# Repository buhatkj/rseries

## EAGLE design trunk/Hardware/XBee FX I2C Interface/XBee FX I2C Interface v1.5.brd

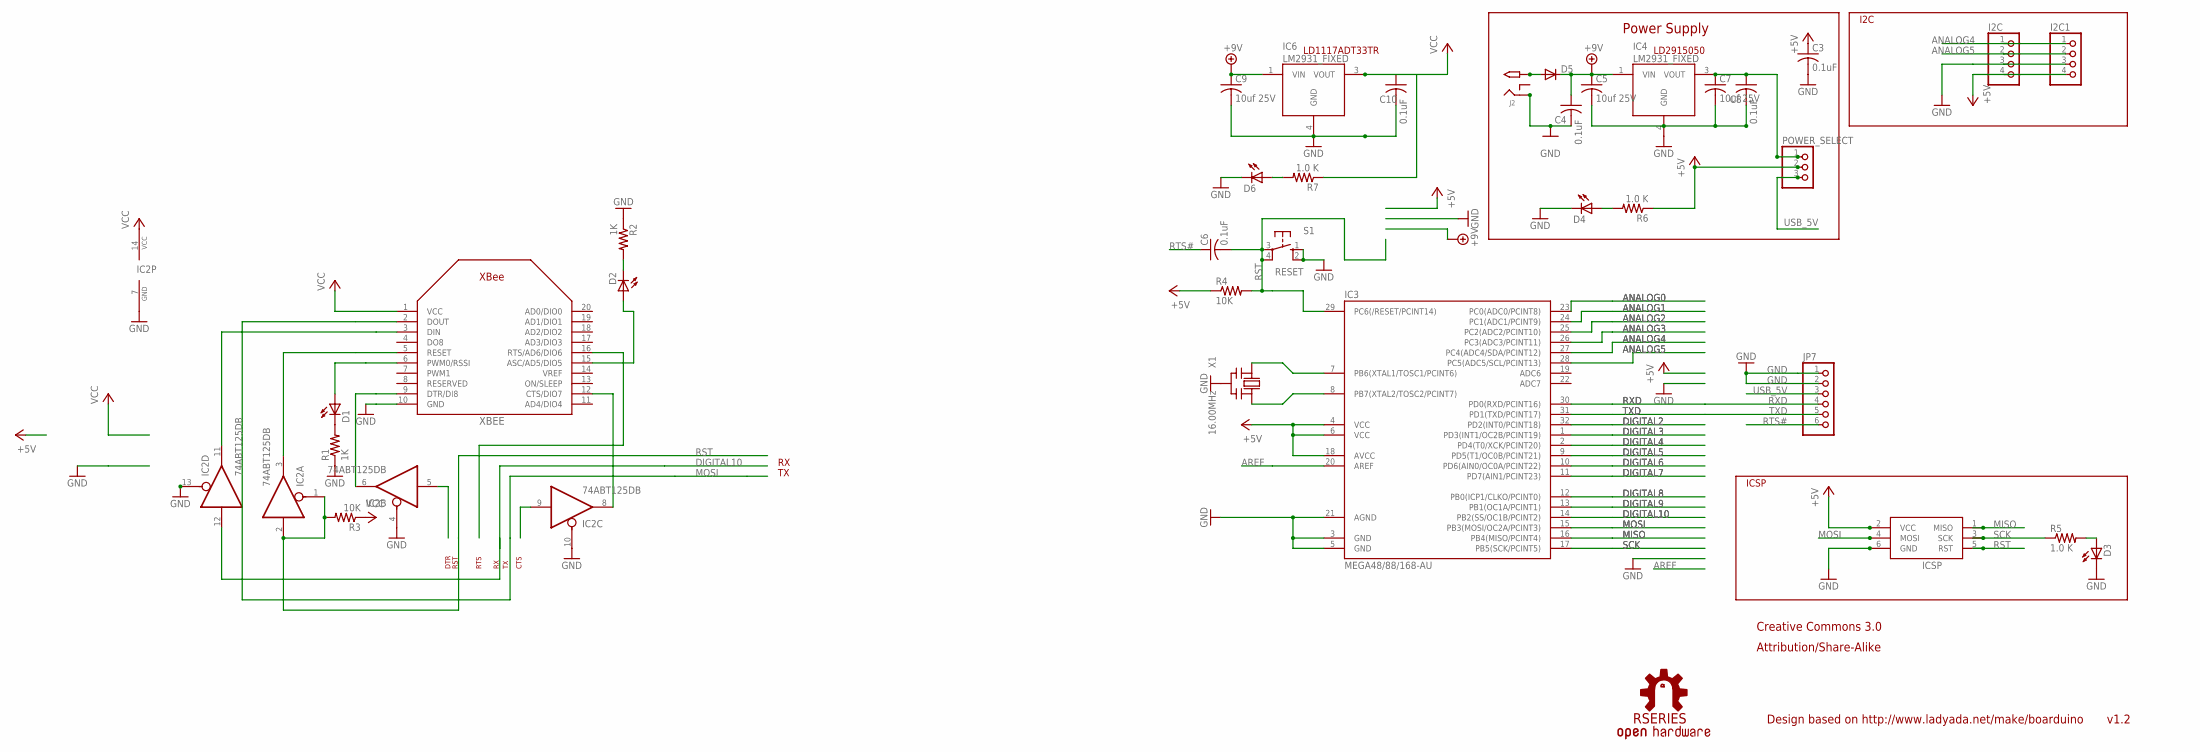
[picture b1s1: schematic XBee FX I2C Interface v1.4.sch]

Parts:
C3, C4, C6, C8, C10: 0.1uF; C1206K
C5, C7, C9: 10uf 25V; C1206K
D1, D2, D4, D6: LEDCHIPLED_1206; CHIPLED_1206
D3: RED; CHIPLED_1206
D5: DIODE-SMB; SMB
I2C, I2C1: PINHD-1X4CB; 1X04-CB
IC2: 74ABT125DB; SSOP14
IC3: MEGA48/88/168-AU; TQFP32-08
IC4, IC6: LM2931_FIXED; DPAK
ICSP: AVRISP-6; AVRISP
J2: 2.1MMJACK; PJ-102A
JP7: PINHD-1X6CLEAN; 1X06-CLEAN
POWER_SELECT: PINHD-1X3; 1X03
R1, R2: 1K; R1206
R3, R4: 10K; R1206
R5, R6, R7: 1.0 K; M1206
S1: RESET; B3F-10XX
U$6: RSERIES-OSHW-LOGOMEDIUM; RSERIES-OSHW-LOGO-MEDIUM
X1: 16.00MHz; CERM_OSC
XBEE: XBEE

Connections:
+3V3: C10.1, IC2.14 (VCC), IC6.3 (VOUT), R3.1, R7.1, XBEE.1 (VCC)
ANALOG0: IC3.23 (PC0(ADC0/PCINT8))
ANALOG1: IC3.24 (PC1(ADC1/PCINT9))
ANALOG2: IC3.25 (PC2(ADC2/PCINT10))
ANALOG3: IC3.26 (PC3(ADC3/PCINT11))
ANALOG4: I2C.1, I2C1.1, IC3.27 (PC4(ADC4/SDA/PCINT12))
ANALOG5: I2C.2, I2C1.2, IC3.28 (PC5(ADC5/SCL/PCINT13))
AREF: IC3.20 (AREF)
DIGITAL2: IC3.32 (PD2(INT0/PCINT18))
DIGITAL3: IC3.1 (PD3(INT1/OC2B/PCINT19))
DIGITAL4: IC3.2 (PD4(T0/XCK/PCINT20))
DIGITAL5: IC3.9 (PD5(T1/OC0B/PCINT21))
DIGITAL6: IC3.10 (PD6(AIN0/OC0A/PCINT22))
DIGITAL7: IC3.11 (PD7(AIN1/PCINT23))
DIGITAL8: IC3.12 (PB0(ICP1/CLKO/PCINT0))
DIGITAL9: IC3.13 (PB1(OC1A/PCINT1))
DIGITAL10: IC2.12 (I), IC3.14 (PB2(SS/OC1B/PCINT2))
GND: C3.2, C4.2, C9.2, C10.2, D3.C, D4.C, D6.C, I2C.3, I2C1.3, IC2.4 (OE), IC2.7 (GND), IC2.10 (OE), IC2.13 (OE), IC3.3 (GND), IC3.5 (GND), IC3.21 (AGND), IC4.4 (GND), IC6.4 (GND), ICSP.6 (GND), J2.RING, JP7.1, JP7.2, R1.1, R2.1, S1.1 (S), S1.2 (S1), X1.P$2 (GND), XBEE.10 (GND)
MISO: IC3.16 (PB4(MISO/PCINT4)), ICSP.1 (MISO)
MOSI: IC3.15 (PB3(MOSI/OC2A/PCINT3)), ICSP.4 (MOSI), XBEE.2 (DOUT)
unnamed: IC2.11 (O), XBEE.3 (DIN)
unnamed: D2.C, R2.2
unnamed: D6.A, R7.2
unnamed: D1.A, XBEE.6 (PWM0/RSSI)
unnamed: D1.C, R1.2
unnamed: IC2.6 (O), XBEE.9 (DTR/DI8)
unnamed: IC2.3 (O), XBEE.5 (RESET)
unnamed: IC2.8 (O), XBEE.12 (CTS/DIO7)
unnamed: D2.A, XBEE.15 (ASC/AD5/DIO5)
unnamed: IC3.7 (PB6(XTAL1/TOSC1/PCINT6)), X1.P$1 (IN)
unnamed: IC3.8 (PB7(XTAL2/TOSC2/PCINT7)), X1.P$3 (OUT)
unnamed: D3.A, R5.2
unnamed: D4.A, R6.2
unnamed: D5.A, J2.TIP
unnamed: C5.2, C7.2, C8.2
unnamed 40: C7.1, C8.1, IC4.3 (VOUT), POWER_SELECT.1; also elsewhere on the board
RST: C6.2, IC2.1 (OE), IC2.2 (I), IC3.29 (PC6(/RESET/PCINT14)), ICSP.5 (RST), R3.2, R4.2, S1.3, S1.4 (P1); also elsewhere on the board
RTS: XBEE.16 (RTS/AD6/DIO6)
RTS#: C6.1, JP7.6
RXD: IC3.30 (PD0(RXD/PCINT16)), JP7.4
SCK: IC3.17 (PB5(SCK/PCINT5)), ICSP.3 (SCK), R5.1
TXD: IC3.31 (PD1(TXD/PCINT17)), JP7.5
USB_5V: JP7.3, POWER_SELECT.3; also elsewhere on the board

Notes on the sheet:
DTR
RST
RTS
CTS
v1.2
Design based on http://www.ladyada.net/make/boarduino
Creative Commons 3.0
Attribution/Share-Alike
I2C
ICSP
Power Supply
LD2915050
LD1117ADT33TR

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
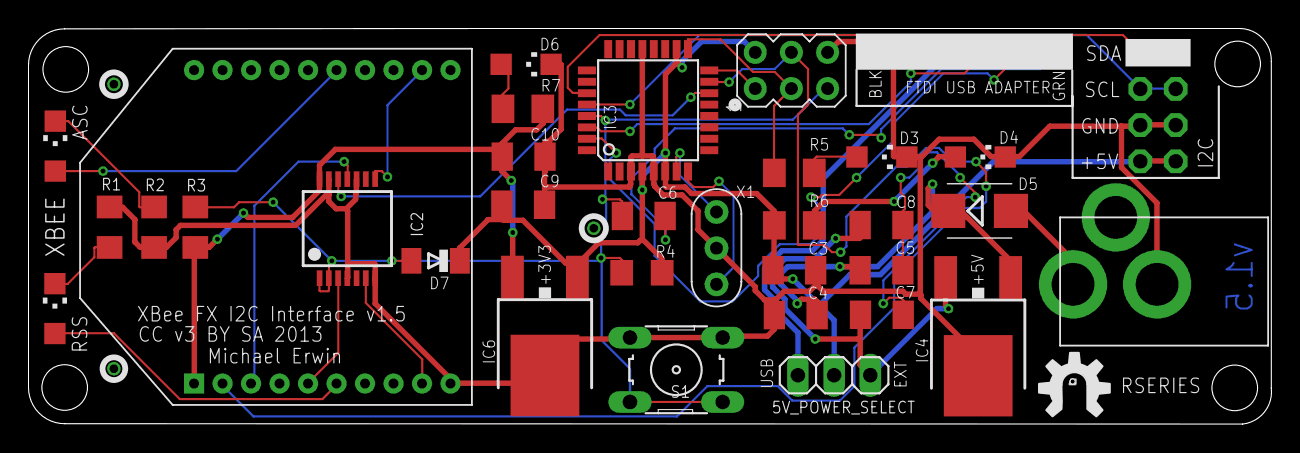
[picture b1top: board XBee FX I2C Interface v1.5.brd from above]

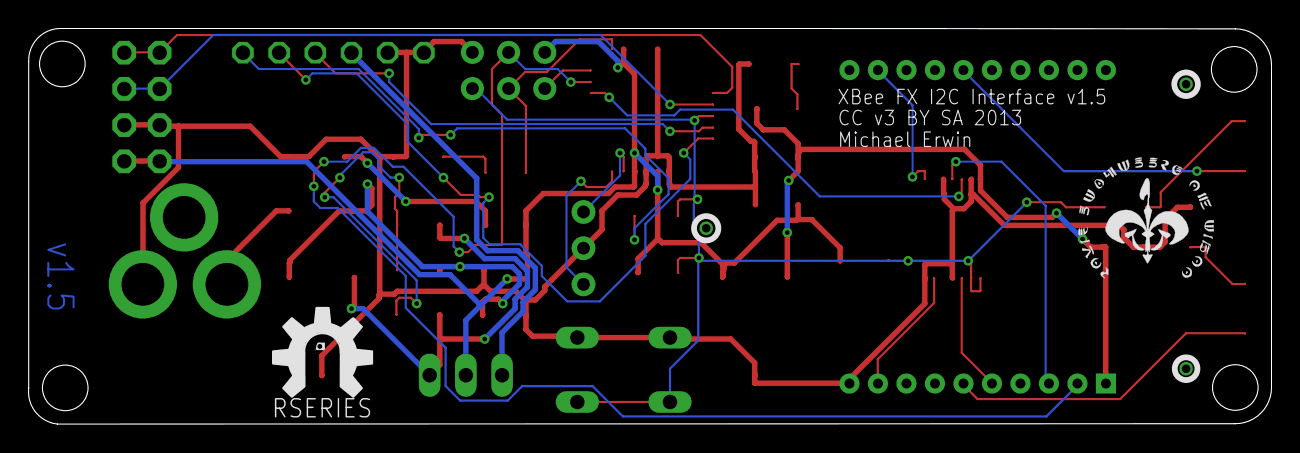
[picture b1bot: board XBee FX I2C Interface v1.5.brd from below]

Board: 2 copper layers, 87.2 x 27.8 mm, 38 parts (2 on the bottom side), 31 nets.

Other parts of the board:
5V_POWER_SELECT: 1X03
D7: CD1206-S01575; MINIMELF
U$2: RSERIES-OSHW-LOGO-LARGE
U$5: ROYAL-ENGINEERS-OF-NABOO-SMALL

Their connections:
unnamed 40: 5V_POWER_SELECT.1; also elsewhere on the board
RST: D7.A; also elsewhere on the board
USB_5V: 5V_POWER_SELECT.3; also elsewhere on the board

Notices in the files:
parts and their libraries:
SparkFun-PowerIC: Licensing: CC v3.0 Share-Alike You are welcome to use this library for commercial purposes.
